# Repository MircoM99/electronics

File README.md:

# Electronics

This repository contains all the files for the design of all the electronics subsystems of the project.

# Repository's Structure

The repository is structured in two main folders of similar arrangement:

- `Test Stand`
  - `\Hardware`
  - `\Software`
  - `\Documents`
  
- `Avionic` 
  - `\Hardware`
  - `\Software`
  - `\Documents`
  
## Hardware

The Hardware folder contains all the project files dedicated to the design of the corrisponding PCB. The Project files are build using the free software [EasyEDA](https://easyeda.com/). Once you have an account on the site, import the project file with the `.json` extension that can be found in the directory path:

- `Avionics\Hardware`

This folder also contains the previous version of the board in:
- `Test Stand\Hardware\Test Stand PCB\OldVersion\OldVersionOnKiCad\Test Stand PCB.pro`

## Software

The software folder contains all the files used to develop the corrisponing subsystem's software.
The files are built using [STM32CubeIDE](https://www.st.com/en/development-tools/stm32cubeide.html).

## Documents

The Documents folder contains all the files and datasheet that have been used to develop all the systems.

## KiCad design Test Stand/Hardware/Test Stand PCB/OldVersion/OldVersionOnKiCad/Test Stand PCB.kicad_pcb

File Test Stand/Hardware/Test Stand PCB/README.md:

# \Hardware

## Cartella di progetto
In questa cartella è contenuto lo schema elettrico della PCB in tutte le sue parti che verrà utilizzato per montare i circuiti nella fase di test. Esiste anche una cartella "OldVersion" che contiene
il vecchio proggetto implementato su KiCad.

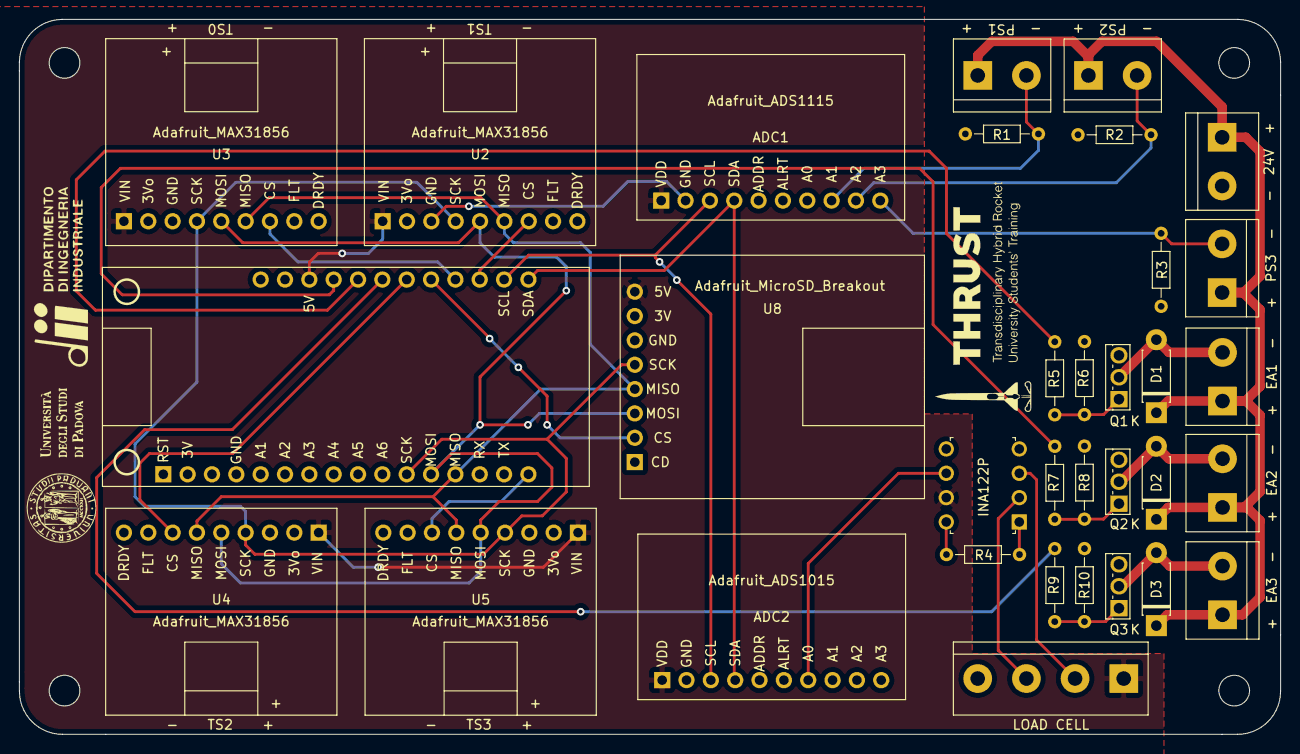
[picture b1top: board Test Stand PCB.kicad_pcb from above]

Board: 2 copper layers, 131.6 x 74.6 mm, 33 parts (0 on the bottom side), 30 nets.

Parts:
+  EA1  -, +  EA2  -, +  EA3  -: Screw_Terminal_01x02; TerminalBlock_bornier-2_P5.08mm
+  PS3  -: Screw_Terminal_01x02; TerminalBlock_bornier-2_P5.08mm
-  24V  +: Screw_Terminal_01x02; TerminalBlock_bornier-2_P5.08mm
-  PS1  +, -  PS2  +: Screw_Terminal_01x02; TerminalBlock_bornier-2_P5.08mm
ADC1: Adafruit_ADS1115
ADC2: Adafruit_ADS1015
D1, D2, D3: D_Schottky; D_DO-41_SOD81_P7.62mm_Horizontal
LOAD CELL: Screw_Terminal_01x04; TerminalBlock_bornier-4_P5.08mm
Q1, Q2, Q3: Q_NMOS_GDS; TO-251-3_Vertical
R1, R2, R3: 200; R_Axial_DIN0204_L3.6mm_D1.6mm_P7.62mm_Horizontal
R4: 4k20; R_Axial_DIN0204_L3.6mm_D1.6mm_P7.62mm_Horizontal
R5, R7, R9: 100; R_Axial_DIN0204_L3.6mm_D1.6mm_P7.62mm_Horizontal
R6, R8, R10: 10k; R_Axial_DIN0204_L3.6mm_D1.6mm_P7.62mm_Horizontal
U1: AdafruitHuzzah32Breakout; Adafruit_Huzzah32
U2, U3, U4, U5: Adafruit_MAX31856
U7: INA_122P
U8: Adafruit_MicroSD_Breakout; Adafruit_MicroSD

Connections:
+5V: ADC1.1, ADC2.1, LOAD CELL.1, U1.26, U2.1, U3.1, U4.1, U5.1, U7.7, U8.8
+24V: + EA1 -.1, + EA2 -.1, + EA3 -.1, + PS3 -.1, - 24V +.1, - PS1 +.1, - PS2 +.1, D1.1, D2.1, D3.1
ADC_A1: - PS1 +.2, ADC1.8, R1.2
ADC_A2: - PS2 +.2, ADC1.9, R2.2
ADC_A3: + PS3 -.2, ADC1.10, R3.2
CS_1: U1.19, U2.7
CS_2: U1.20, U3.7
CS_3: U1.22, U4.7
CS_4: U1.16, U5.7
CS_5: U1.21, U8.2
FET_Gate1: R5.1, U1.24
FET_Gate2: R7.1, U1.25
FET_Gate3: R9.1, U1.23
GND: - 24V +.2, ADC1.2, ADC1.7, ADC2.2, ADC2.8, ADC2.9, ADC2.10, LOAD CELL.4, Q1.3, Q2.3, Q3.3, R1.1, R2.1, R3.1, R6.2, R8.2, R10.2, U1.4, U2.3, U3.3, U4.3, U5.3, U7.4, U7.5, U8.6
I2C_SCL: ADC1.3, ADC2.3, U1.18
I2C_SDA: ADC1.4, ADC2.4, U1.17
LOAD_CELL_VOLTAGE: ADC2.7, U7.6
unnamed: + EA1 -.2, D1.2, Q1.2
unnamed: + EA2 -.2, D2.2, Q2.2
unnamed: + EA3 -.2, D3.2, Q3.2
unnamed: LOAD CELL.2, U7.3
unnamed: LOAD CELL.3, U7.2
unnamed: Q1.1, R5.2, R6.1
unnamed: Q2.1, R7.2, R8.1
unnamed: Q3.1, R9.2, R10.1
unnamed: R4.1, U7.8
unnamed: R4.2, U7.1
SPI_MISO: U1.13, U2.6, U3.6, U4.6, U5.6, U8.4
SPI_MOSI: U1.12, U2.5, U3.5, U4.5, U5.5, U8.3
SPI_SCK: U1.11, U2.4, U3.4, U4.4, U5.4, U8.5

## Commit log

2020-11-17 Upload di documentazione e design file per il PCB
2020-11-17 Updated Component selection spreadsheet and PCB schematics
2020-11-18 Updated PCB schematic pdf
2020-11-18 Changed the repository structure
2020-11-18 Update Readme.md with repository explanation
2020-11-18 Created Documentation links for Test stand electonic components
2020-11-23 Updated documentation structure
2020-11-23 Update file names and upload of the schematic template
2020-11-24 Aggiunta bozza campagna di test
    Posizione del documento provvisoria, metto in electronics per comodità per Jacopo
2020-11-26 Updated Test schematic and PCB Design
2020-12-05 Added gerber file for manufacturing of Test Stand PCB v1.0
2020-12-31 Updated Schematic PDF
2020-12-31 Updated PDF schematics
2020-12-31 Rifatti i calcoli considerando impilati i componenti
2021-02-19 figure
2021-02-19 aggiunta pid con evidenziati sensori e elettrovalvole
2021-03-02 Uploading of the Rev1.1 Board
    Rev1.1 Board, changes:
    - Added 2 more Electronic actuator circuit drivers
    - Changed screw terminal layout
    - Added Front and Back Silckscreen
    - Improved Layout
    - Changed resistor footprint
2021-03-13 Added Mounting Holes
2021-03-13 Upload PCB images and Updated Dimensionamento elettronica preliminare
2021-03-13 Cut PCB Images
2021-03-13 Spostato Dimensionamento preliminare
2021-03-19 update figure
2021-04-17 Archie Figures
2021-04-17 Corrected .png
2022-03-13 upload
2022-08-11 Lista cose da comprare
    Modifica dei componenti e inserimento di una bozza della lista delle cose da comprare
2022-12-18 Aggiornamento lavori 2022
    Sono stati aggiornati la maggior parte dei files con le modifiche adottate nel 2022. La sezione Test Stand contiene ancora del vecchio materiale che verrà sostituito non appena disponibile.
2022-12-23 STM32 Software
    Inserimento del progetto su STM32CubeIDE per il software da usare nella fase di test
2022-12-28 Rimozione Progetto
    Rimozione Progetto per bug nel codice
2022-12-28 Aggiunta readme
2022-12-28 Programma per i test
    Sistema di acquisizione dati con STM32F411 su Nucleo board F411RE
2022-12-30 Lavori assegnati
    Descrizione precisa dei compiti assegnati
